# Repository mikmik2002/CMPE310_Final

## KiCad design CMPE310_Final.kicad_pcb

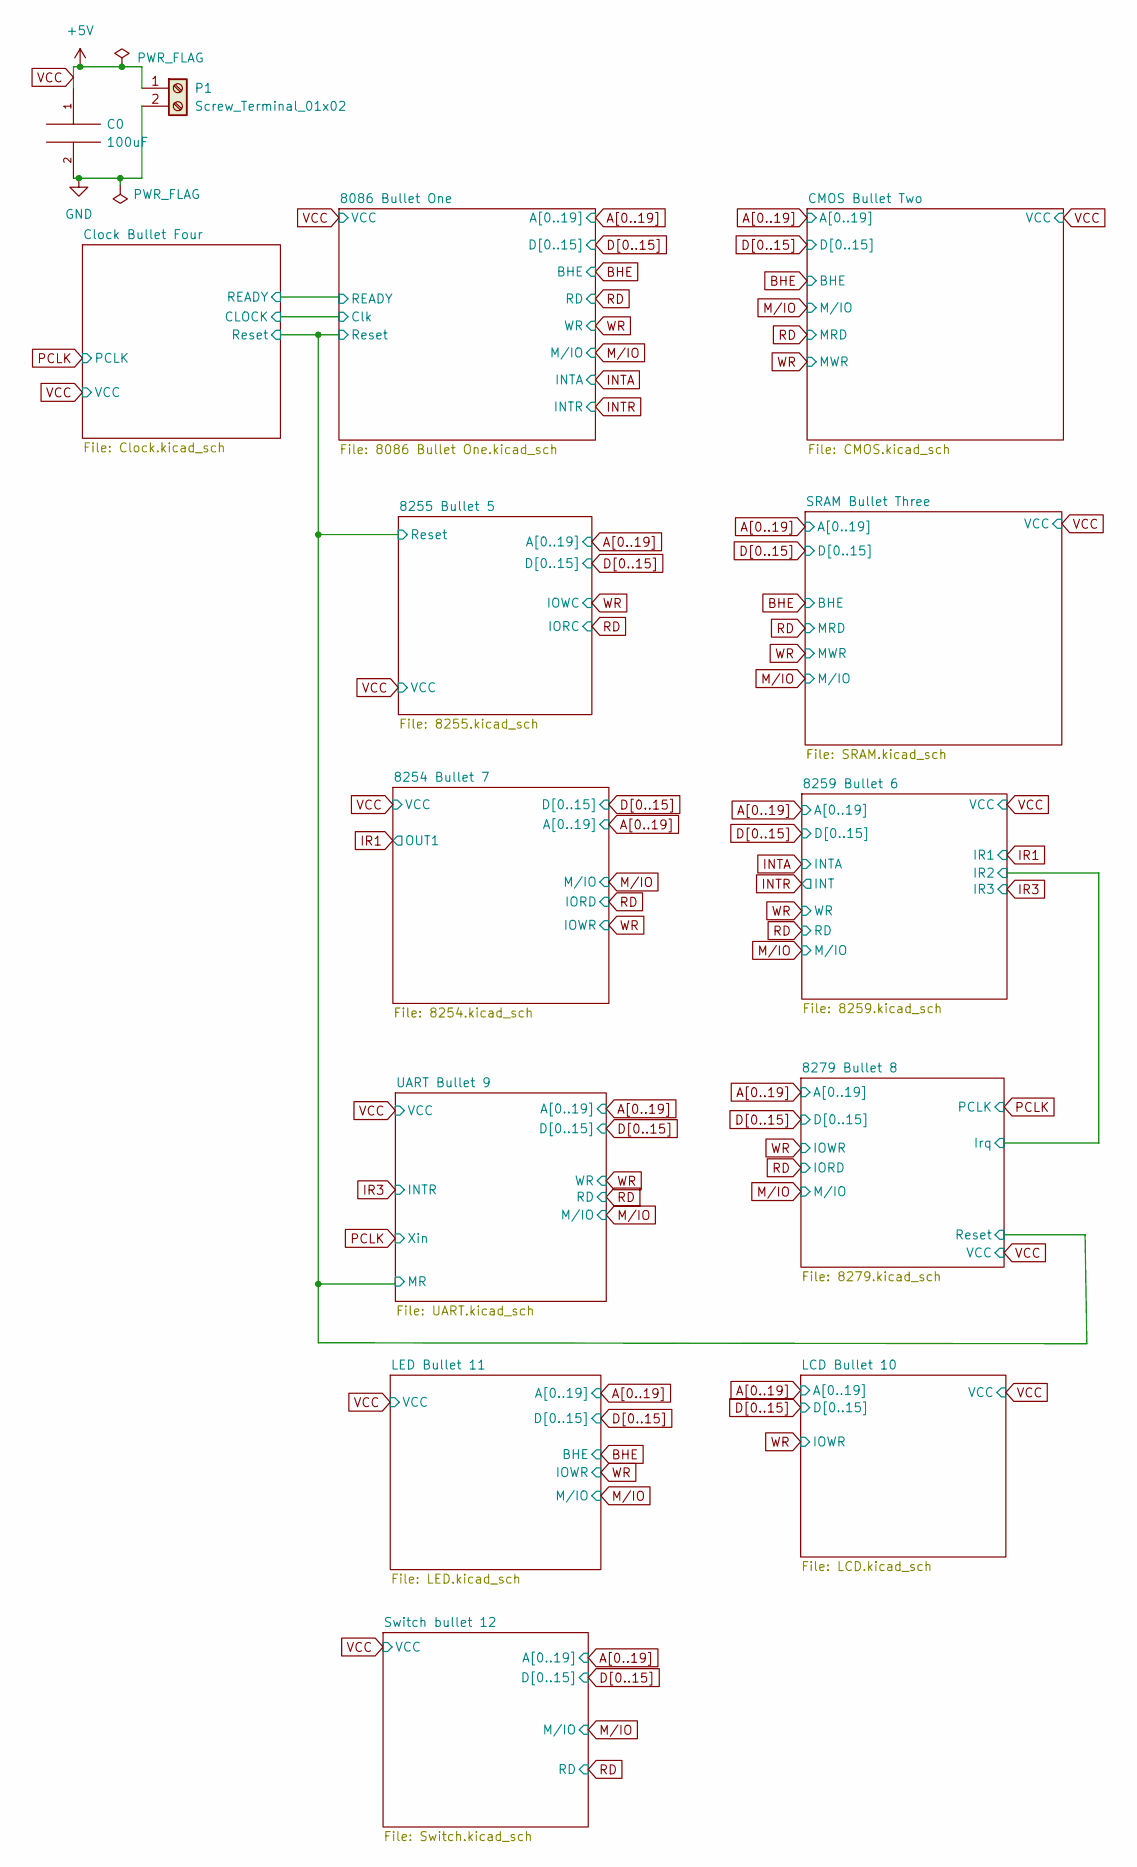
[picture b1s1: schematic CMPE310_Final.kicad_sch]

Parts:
C0: 100uF; CP_Axial_L10.0mm_D4.5mm_P15.00mm_Horizontal
P1: Screw_Terminal_01x02; TerminalBlock_Altech_AK300-2_P5.00mm

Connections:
GND: C0.2, P1.2; also elsewhere on the board
VCC: C0.1, P1.1; also elsewhere on the board

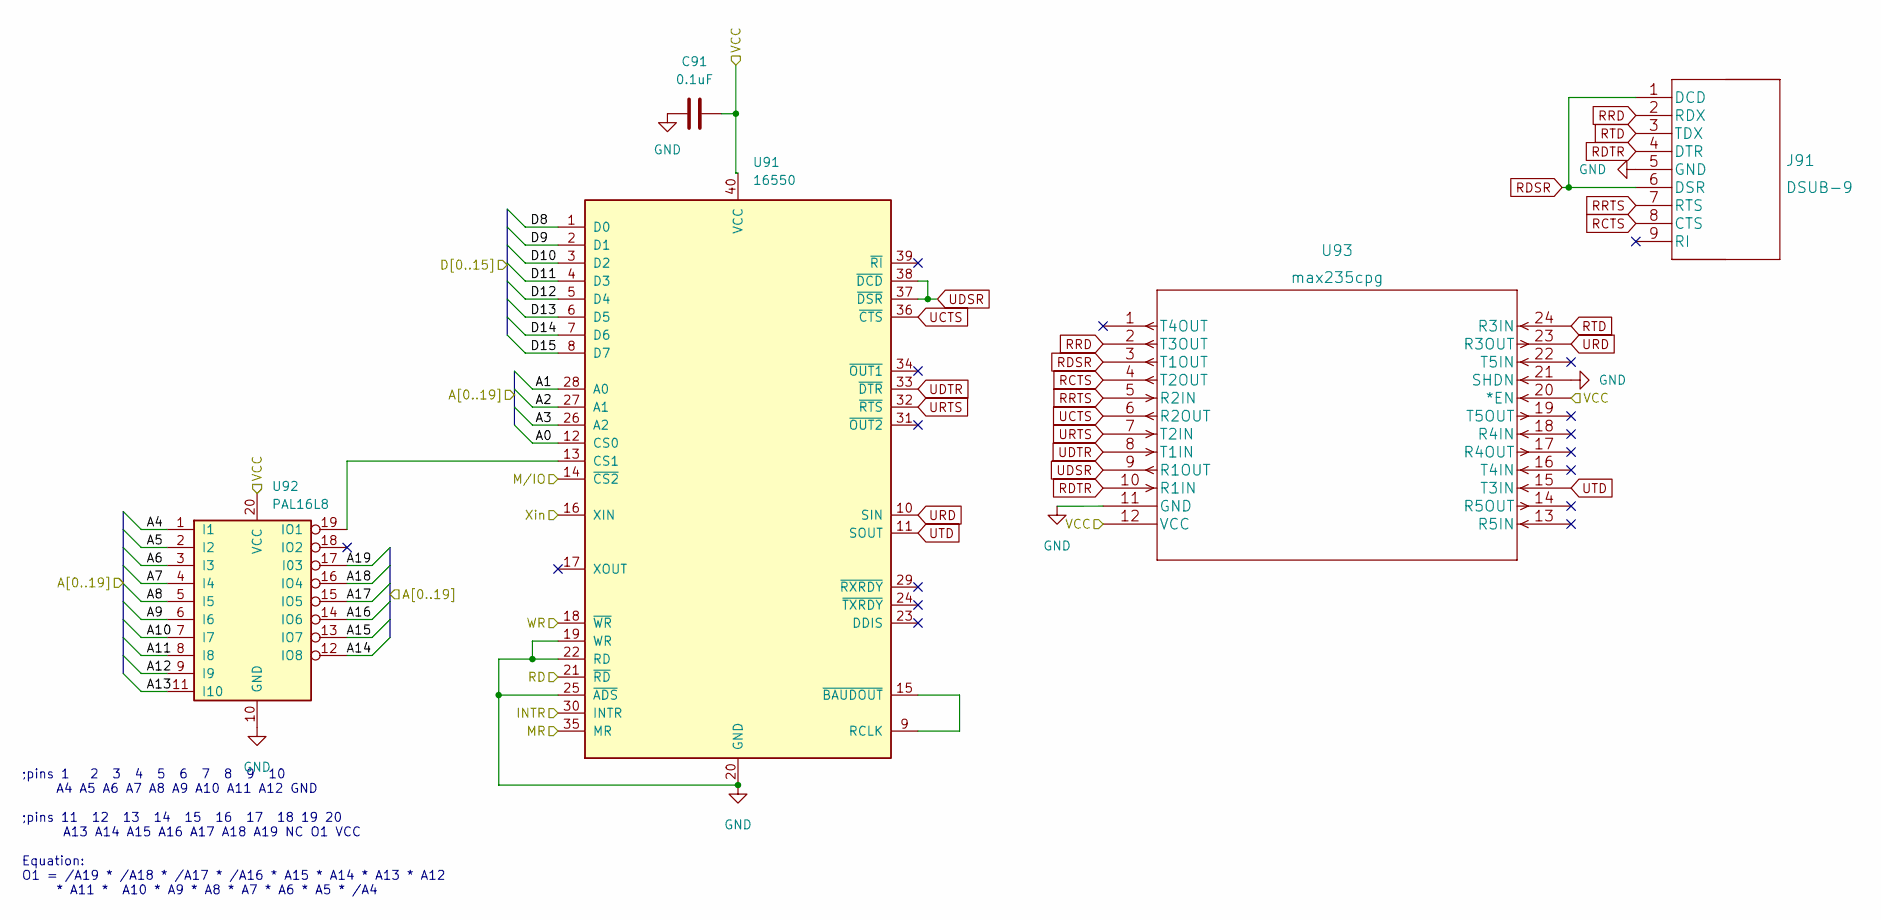
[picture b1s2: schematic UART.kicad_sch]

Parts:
C91: 0.1uF; C_Axial_L3.8mm_D2.6mm_P7.50mm_Horizontal
J91: DSUB-9
U91: 16550; DIP-40_W15.24mm
U92: PAL16L8; DIP-20_W7.62mm
U93: max235cpg

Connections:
/8086 Bullet One/Reset: U91.35 (MR); also elsewhere on the board
A0: U91.12 (CS0); also elsewhere on the board
A1: U91.28 (A0); also elsewhere on the board
A2: U91.27 (A1); also elsewhere on the board
A3: U91.26 (A2); also elsewhere on the board
A4: U92.1 (I1); also elsewhere on the board
A5: U92.2 (I2); also elsewhere on the board
A6: U92.3 (I3); also elsewhere on the board
A7: U92.4 (I4); also elsewhere on the board
A8: U92.5 (I5); also elsewhere on the board
A9: U92.6 (I6); also elsewhere on the board
A10: U92.7 (I7); also elsewhere on the board
A11: U92.8 (I8); also elsewhere on the board
A12: U92.9 (I9); also elsewhere on the board
A13: U92.11 (I10); also elsewhere on the board
A14: U92.12 (IO8); also elsewhere on the board
A15: U92.13 (IO7); also elsewhere on the board
A16: U92.14 (IO6); also elsewhere on the board
A17: U92.15 (IO5); also elsewhere on the board
A18: U92.16 (IO4); also elsewhere on the board
A19: U92.17 (I03); also elsewhere on the board
D8: U91.1 (D0); also elsewhere on the board
D9: U91.2 (D1); also elsewhere on the board
D10: U91.3 (D2); also elsewhere on the board
D11: U91.4 (D3); also elsewhere on the board
D12: U91.5 (D4); also elsewhere on the board
D13: U91.6 (D5); also elsewhere on the board
D14: U91.7 (D6); also elsewhere on the board
D15: U91.8 (D7); also elsewhere on the board
GND: C91.1, J91.5 (GND), U91.19 (WR), U91.20 (GND), U91.22 (RD), U91.25 (~ADS), U92.10 (GND), U93.11 (GND), U93.21 (SHDN); also elsewhere on the board
IR3: U91.30 (INTR); also elsewhere on the board
M/IO: U91.14 (~CS2); also elsewhere on the board
unnamed: U91.13 (CS1), U92.19 (IO1)
unnamed: U91.9 (RCLK), U91.15 (~BAUDOUT)
PCLK: U91.16 (XIN); also elsewhere on the board
RCTS: J91.8 (CTS), U93.4 (T2OUT)
RD: U91.21 (~RD); also elsewhere on the board
RDSR: J91.1 (DCD), J91.6 (DSR), U93.3 (T1OUT)
RDTR: J91.4 (DTR), U93.10 (R1IN)
RRD: J91.2 (RDX), U93.2 (T3OUT)
RRTS: J91.7 (RTS), U93.5 (R2IN)
RTD: J91.3 (TDX), U93.24 (R3IN)
UCTS: U91.36 (~CTS), U93.6 (R2OUT)
UDSR: U91.37 (~DSR), U91.38 (~DCD), U93.9 (R1OUT)
UDTR: U91.33 (~DTR), U93.8 (T1IN)
URD: U91.10 (SIN), U93.23 (R3OUT)
URTS: U91.32 (~RTS), U93.7 (T2IN)
UTD: U91.11 (SOUT), U93.15 (T3IN)
VCC: C91.2, U91.40 (VCC), U92.20 (VCC), U93.12 (VCC), U93.20 (*EN); also elsewhere on the board
WR: U91.18 (~WR); also elsewhere on the board

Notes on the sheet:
;pins 1 2 3 4 5 6 7 8 9 10 A4 A5 A6 A7 A8 A9 A10 A11 A12 GND ;pins 11 12 13 14 15 16 17 18 19 20 A13 A14 A15 A16 A17 A18 A19 NC O1 VCC Equation: O1 = /A19 * /A18 * /A17 * /A16 * A15 * A14 * A13 * A12 * A11 * A10 * A9 * A8 * A7 * A6 * A5 * /A4

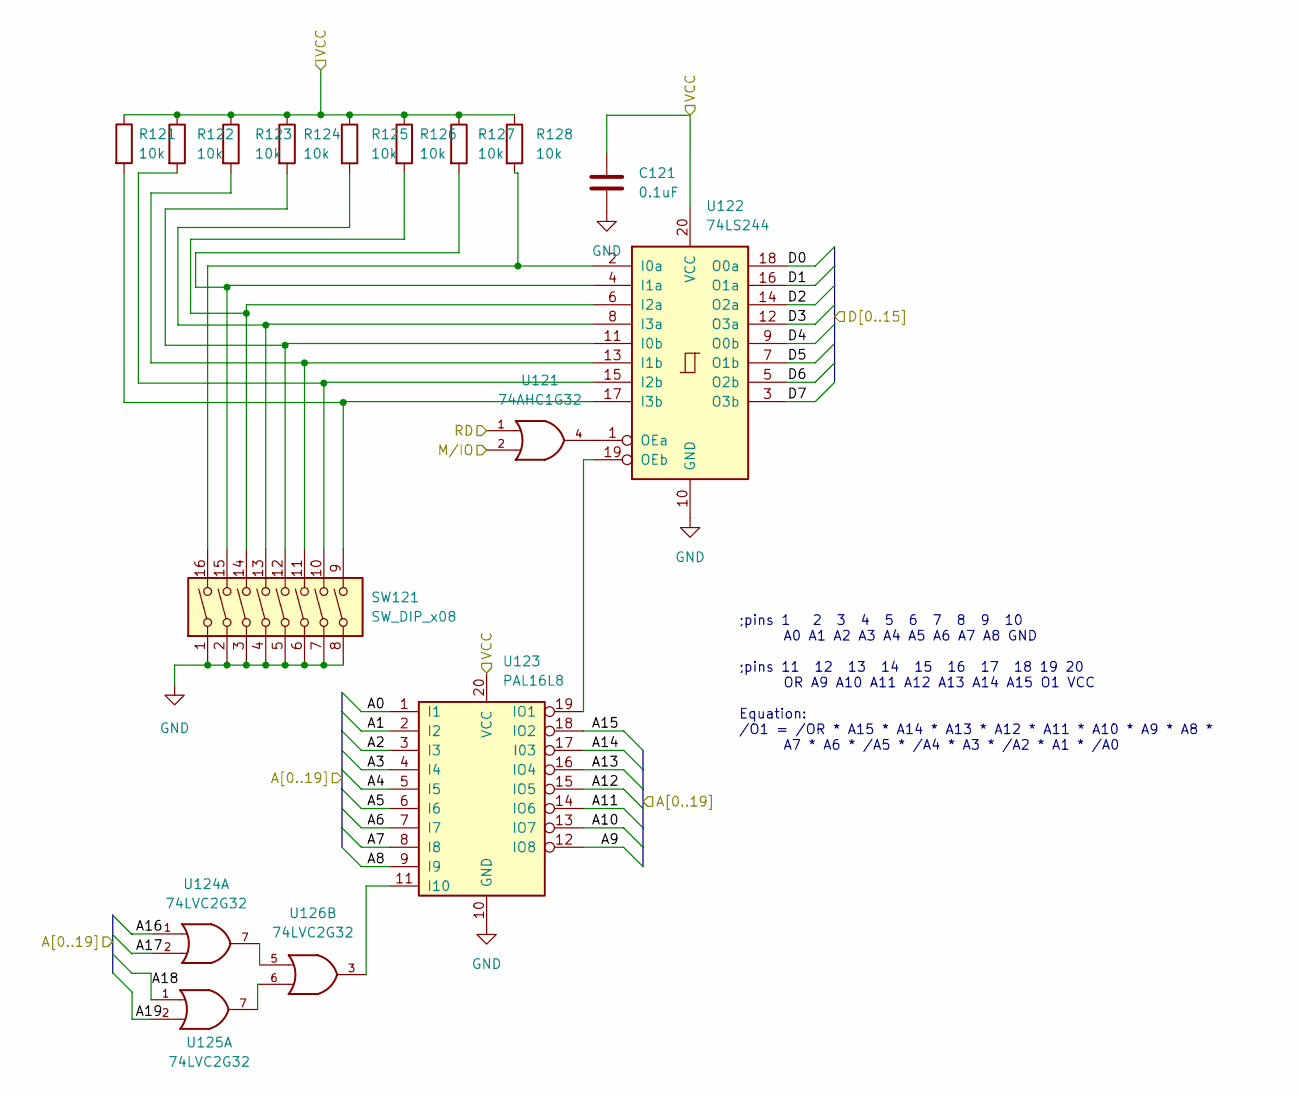
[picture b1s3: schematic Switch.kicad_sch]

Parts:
C121: 0.1uF; C_Axial_L3.8mm_D2.6mm_P7.50mm_Horizontal
R121, R122, R123, R124, R125, R126, R127, R128: 10k; R_Axial_DIN0204_L3.6mm_D1.6mm_P1.90mm_Vertical
SW121: SW_DIP_x08; SW_DIP_SPSTx08_Slide_6.7x21.88mm_W7.62mm_P2.54mm_LowProfile
U121: 74AHC1G32; SOT-23-5
U122: 74LS244; DIP-20_W7.62mm
U123: PAL16L8; DIP-20_W7.62mm
U124, U125, U126: 74LVC2G32

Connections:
A0: U123.1 (I1); also elsewhere on the board
A1: U123.2 (I2); also elsewhere on the board
A2: U123.3 (I3); also elsewhere on the board
A3: U123.4 (I4); also elsewhere on the board
A4: U123.5 (I5); also elsewhere on the board
A5: U123.6 (I6); also elsewhere on the board
A6: U123.7 (I7); also elsewhere on the board
A7: U123.8 (I8); also elsewhere on the board
A8: U123.9 (I9); also elsewhere on the board
A9: U123.12 (IO8); also elsewhere on the board
A10: U123.13 (IO7); also elsewhere on the board
A11: U123.14 (IO6); also elsewhere on the board
A12: U123.15 (IO5); also elsewhere on the board
A13: U123.16 (IO4); also elsewhere on the board
A14: U123.17 (I03); also elsewhere on the board
A15: U123.18 (IO2); also elsewhere on the board
A16: U124.1; also elsewhere on the board
A17: U124.2; also elsewhere on the board
A18: U125.1; also elsewhere on the board
A19: U125.2; also elsewhere on the board
D0: U122.18 (O0a); also elsewhere on the board
D1: U122.16 (O1a); also elsewhere on the board
D2: U122.14 (O2a); also elsewhere on the board
D3: U122.12 (O3a); also elsewhere on the board
D4: U122.9 (O0b); also elsewhere on the board
D5: U122.7 (O1b); also elsewhere on the board
D6: U122.5 (O2b); also elsewhere on the board
D7: U122.3 (O3b); also elsewhere on the board
GND: C121.2, SW121.1, SW121.2, SW121.3, SW121.4, SW121.5, SW121.6, SW121.7, SW121.8, U121.3 (GND), U122.10 (GND), U123.10 (GND), U124.4 (GND), U125.4 (GND), U126.4 (GND); also elsewhere on the board
M/IO: U121.2; also elsewhere on the board
unnamed: R121.2, SW121.9, U122.17 (I3b)
unnamed: R122.2, SW121.10, U122.15 (I2b)
unnamed: R123.2, SW121.11, U122.13 (I1b)
unnamed: R124.2, SW121.12, U122.11 (I0b)
unnamed: R125.2, SW121.13, U122.8 (I3a)
unnamed: R126.2, SW121.14, U122.6 (I2a)
unnamed: R127.2, SW121.15, U122.4 (I1a)
unnamed: R128.2, SW121.16, U122.2 (I0a)
unnamed: U121.4, U122.1 (OEa)
unnamed: U122.19 (OEb), U123.19 (IO1)
unnamed: U123.11 (I10), U126.3
unnamed: U124.7, U126.5
unnamed: U125.7, U126.6
RD: U121.1; also elsewhere on the board
VCC: C121.1, R121.1, R122.1, R123.1, R124.1, R125.1, R126.1, R127.1, R128.1, U121.5 (VCC), U122.20 (VCC), U123.20 (VCC), U124.8 (VCC), U125.8 (VCC), U126.8 (VCC); also elsewhere on the board

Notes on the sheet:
;pins 1 2 3 4 5 6 7 8 9 10 A0 A1 A2 A3 A4 A5 A6 A7 A8 GND ;pins 11 12 13 14 15 16 17 18 19 20 OR A9 A10 A11 A12 A13 A14 A15 O1 VCC Equation: /O1 = /OR * A15 * A14 * A13 * A12 * A11 * A10 * A9 * A8 * A7 * A6 * /A5 * /A4 * A3 * /A2 * A1 * /A0

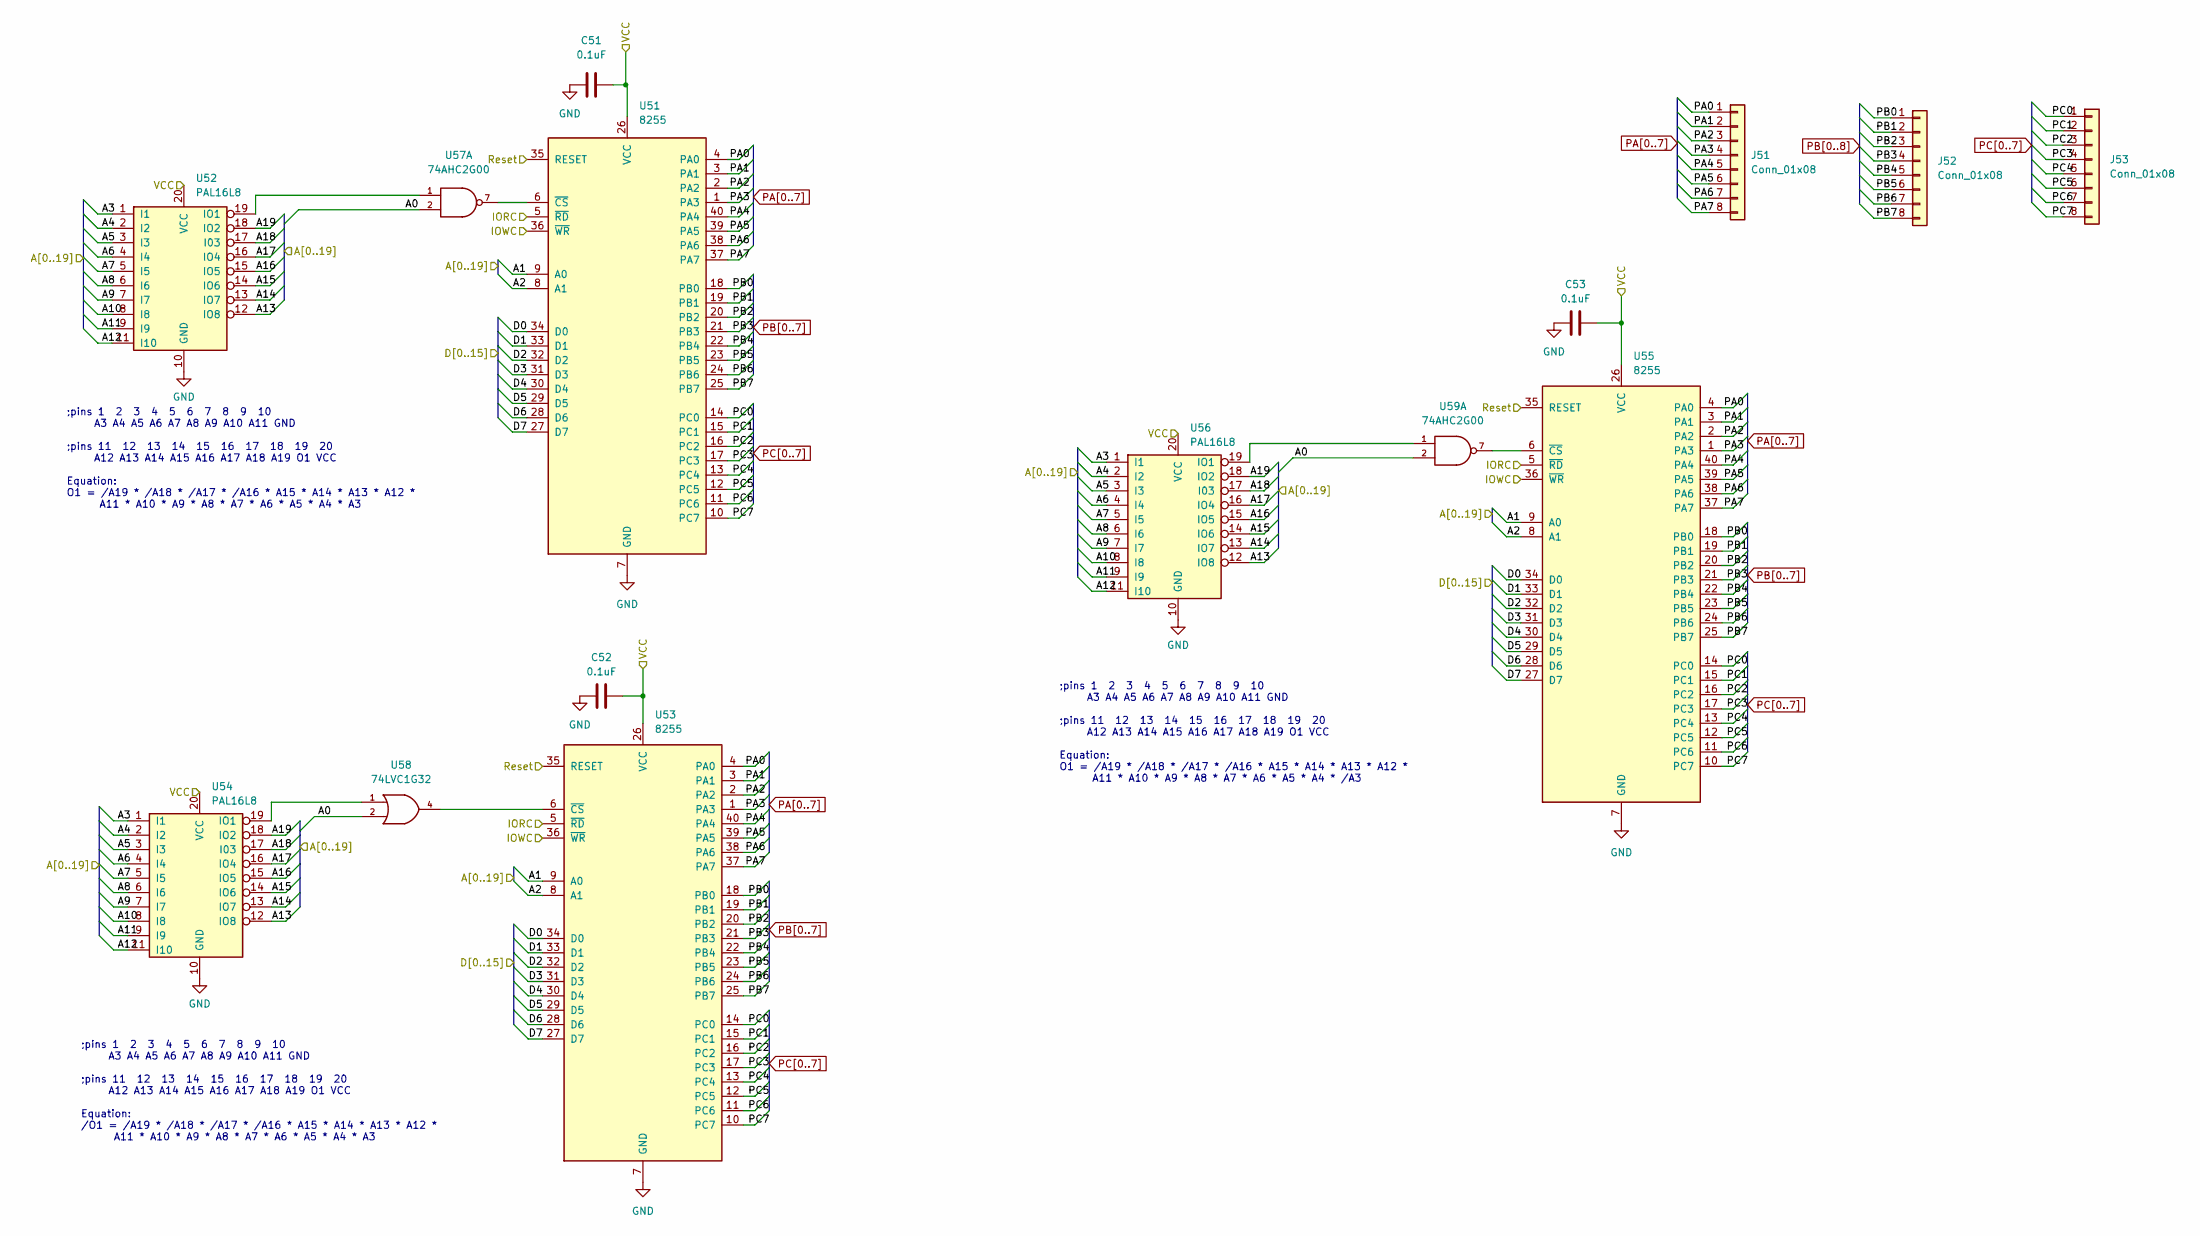
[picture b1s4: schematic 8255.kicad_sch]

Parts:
C51, C52, C53: 0.1uF; C_Axial_L3.8mm_D2.6mm_P7.50mm_Horizontal
J51, J52, J53: Conn_01x08; PinHeader_1x08_P1.00mm_Vertical
U51, U53, U55: 8255; DIP-40_W15.24mm
U52, U54, U56: PAL16L8; DIP-20_W7.62mm
U57, U59: 74AHC2G00
U58: 74LVC1G32

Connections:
/8086 Bullet One/Reset: U51.35 (RESET), U53.35 (RESET), U55.35 (RESET); also elsewhere on the board
A0: U57.2, U58.2, U59.2; also elsewhere on the board
A1: U51.9 (A0), U53.9 (A0), U55.9 (A0); also elsewhere on the board
A2: U51.8 (A1), U53.8 (A1), U55.8 (A1); also elsewhere on the board
A3: U52.1 (I1), U54.1 (I1), U56.1 (I1); also elsewhere on the board
A4: U52.2 (I2), U54.2 (I2), U56.2 (I2); also elsewhere on the board
A5: U52.3 (I3), U54.3 (I3), U56.3 (I3); also elsewhere on the board
A6: U52.4 (I4), U54.4 (I4), U56.4 (I4); also elsewhere on the board
A7: U52.5 (I5), U54.5 (I5), U56.5 (I5); also elsewhere on the board
A8: U52.6 (I6), U54.6 (I6), U56.6 (I6); also elsewhere on the board
A9: U52.7 (I7), U54.7 (I7), U56.7 (I7); also elsewhere on the board
A10: U52.8 (I8), U54.8 (I8), U56.8 (I8); also elsewhere on the board
A11: U52.9 (I9), U54.9 (I9), U56.9 (I9); also elsewhere on the board
A12: U52.11 (I10), U54.11 (I10), U56.11 (I10); also elsewhere on the board
A13: U52.12 (IO8), U54.12 (IO8), U56.12 (IO8); also elsewhere on the board
A14: U52.13 (IO7), U54.13 (IO7), U56.13 (IO7); also elsewhere on the board
A15: U52.14 (IO6), U54.14 (IO6), U56.14 (IO6); also elsewhere on the board
A16: U52.15 (IO5), U54.15 (IO5), U56.15 (IO5); also elsewhere on the board
A17: U52.16 (IO4), U54.16 (IO4), U56.16 (IO4); also elsewhere on the board
A18: U52.17 (I03), U54.17 (I03), U56.17 (I03); also elsewhere on the board
A19: U52.18 (IO2), U54.18 (IO2), U56.18 (IO2); also elsewhere on the board
D0: U51.34 (D0), U53.34 (D0), U55.34 (D0); also elsewhere on the board
D1: U51.33 (D1), U53.33 (D1), U55.33 (D1); also elsewhere on the board
D2: U51.32 (D2), U53.32 (D2), U55.32 (D2); also elsewhere on the board
D3: U51.31 (D3), U53.31 (D3), U55.31 (D3); also elsewhere on the board
D4: U51.30 (D4), U53.30 (D4), U55.30 (D4); also elsewhere on the board
D5: U51.29 (D5), U53.29 (D5), U55.29 (D5); also elsewhere on the board
D6: U51.28 (D6), U53.28 (D6), U55.28 (D6); also elsewhere on the board
D7: U51.27 (D7), U53.27 (D7), U55.27 (D7); also elsewhere on the board
GND: C51.1, C52.1, C53.1, U51.7 (GND), U52.10 (GND), U53.7 (GND), U54.10 (GND), U55.7 (GND), U56.10 (GND), U57.4 (GND), U58.3 (GND), U59.4 (GND); also elsewhere on the board
unnamed: U51.6 (~CS), U57.7
unnamed: U52.19 (IO1), U57.1
unnamed: U53.6 (~CS), U58.4
unnamed: U54.19 (IO1), U58.1
unnamed: U55.6 (~CS), U59.7
unnamed: U56.19 (IO1), U59.1
PA0: J51.1, U51.4 (PA0), U53.4 (PA0), U55.4 (PA0)
PA1: J51.2, U51.3 (PA1), U53.3 (PA1), U55.3 (PA1)
PA2: J51.3, U51.2 (PA2), U53.2 (PA2), U55.2 (PA2)
PA3: J51.4, U51.1 (PA3), U53.1 (PA3), U55.1 (PA3)
PA4: J51.5, U51.40 (PA4), U53.40 (PA4), U55.40 (PA4)
PA5: J51.6, U51.39 (PA5), U53.39 (PA5), U55.39 (PA5)
PA6: J51.7, U51.38 (PA6), U53.38 (PA6), U55.38 (PA6)
PA7: J51.8, U51.37 (PA7), U53.37 (PA7), U55.37 (PA7)
PB0: J52.1, U51.18 (PB0), U53.18 (PB0), U55.18 (PB0)
PB1: J52.2, U51.19 (PB1), U53.19 (PB1), U55.19 (PB1)
PB2: J52.3, U51.20 (PB2), U53.20 (PB2), U55.20 (PB2)
PB3: J52.4, U51.21 (PB3), U53.21 (PB3), U55.21 (PB3)
PB4: J52.5, U51.22 (PB4), U53.22 (PB4), U55.22 (PB4)
PB5: J52.6, U51.23 (PB5), U53.23 (PB5), U55.23 (PB5)
PB6: J52.7, U51.24 (PB6), U53.24 (PB6), U55.24 (PB6)
PB7: J52.8, U51.25 (PB7), U53.25 (PB7), U55.25 (PB7)
PC0: J53.1, U51.14 (PC0), U53.14 (PC0), U55.14 (PC0)
PC1: J53.2, U51.15 (PC1), U53.15 (PC1), U55.15 (PC1)
PC2: J53.3, U51.16 (PC2), U53.16 (PC2), U55.16 (PC2)
PC3: J53.4, U51.17 (PC3), U53.17 (PC3), U55.17 (PC3)
PC4: J53.5, U51.13 (PC4), U53.13 (PC4), U55.13 (PC4)
PC5: J53.6, U51.12 (PC5), U53.12 (PC5), U55.12 (PC5)
PC6: J53.7, U51.11 (PC6), U53.11 (PC6), U55.11 (PC6)
PC7: J53.8, U51.10 (PC7), U53.10 (PC7), U55.10 (PC7)
RD: U51.5 (~RD), U53.5 (~RD), U55.5 (~RD); also elsewhere on the board
VCC: C51.2, C52.2, C53.2, U51.26 (VCC), U52.20 (VCC), U53.26 (VCC), U54.20 (VCC), U55.26 (VCC), U56.20 (VCC), U57.8 (VCC), U59.8 (VCC); also elsewhere on the board
WR: U51.36 (~WR), U53.36 (~WR), U55.36 (~WR); also elsewhere on the board

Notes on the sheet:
;pins 1 2 3 4 5 6 7 8 9 10 A3 A4 A5 A6 A7 A8 A9 A10 A11 GND ;pins 11 12 13 14 15 16 17 18 19 20 A12 A13 A14 A15 A16 A17 A18 A19 O1 VCC Equation: O1 = /A19 * /A18 * /A17 * /A16 * A15 * A14 * A13 * A12 * A11 * A10 * A9 * A8 * A7 * A6 * A5 * A4 * A3
;pins 1 2 3 4 5 6 7 8 9 10 A3 A4 A5 A6 A7 A8 A9 A10 A11 GND ;pins 11 12 13 14 15 16 17 18 19 20 A12 A13 A14 A15 A16 A17 A18 A19 O1 VCC Equation: /O1 = /A19 * /A18 * /A17 * /A16 * A15 * A14 * A13 * A12 * A11 * A10 * A9 * A8 * A7 * A6 * A5 * A4 * A3
;pins 1 2 3 4 5 6 7 8 9 10 A3 A4 A5 A6 A7 A8 A9 A10 A11 GND ;pins 11 12 13 14 15 16 17 18 19 20 A12 A13 A14 A15 A16 A17 A18 A19 O1 VCC Equation: O1 = /A19 * /A18 * /A17 * /A16 * A15 * A14 * A13 * A12 * A11 * A10 * A9 * A8 * A7 * A6 * A5 * A4 * /A3

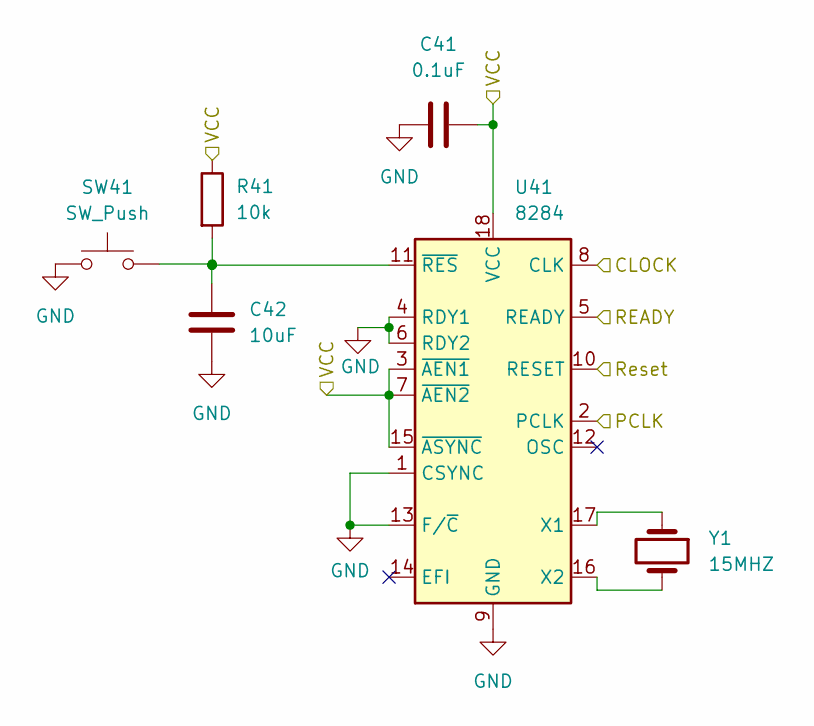
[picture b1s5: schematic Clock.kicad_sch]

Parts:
C41: 0.1uF; C_Axial_L3.8mm_D2.6mm_P7.50mm_Horizontal
C42: 10uF; C_Axial_L3.8mm_D2.6mm_P7.50mm_Horizontal
R41: 10k; R_Axial_DIN0204_L3.6mm_D1.6mm_P1.90mm_Vertical
SW41: SW_Push; SW_Tactile_Straight_KSA0Axx1LFTR
U41: 8284; DIP-18_W7.62mm
Y1: 15MHZ; Crystal_AT310_D3.0mm_L10.0mm_Vertical

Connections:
/8086 Bullet One/Clk: U41.8 (CLK); also elsewhere on the board
/8086 Bullet One/READY: U41.5 (READY); also elsewhere on the board
/8086 Bullet One/Reset: U41.10 (RESET); also elsewhere on the board
GND: C41.1, C42.2, SW41.1, U41.1 (CSYNC), U41.4 (RDY1), U41.6 (RDY2), U41.9 (GND), U41.13 (F/~C); also elsewhere on the board
unnamed: C42.1, R41.2, SW41.2, U41.11 (~RES)
unnamed: U41.16 (X2), Y1.2
unnamed: U41.17 (X1), Y1.1
PCLK: U41.2 (PCLK); also elsewhere on the board
VCC: C41.2, R41.1, U41.3 (~AEN1), U41.7 (~AEN2), U41.15 (~ASYNC), U41.18 (VCC); also elsewhere on the board

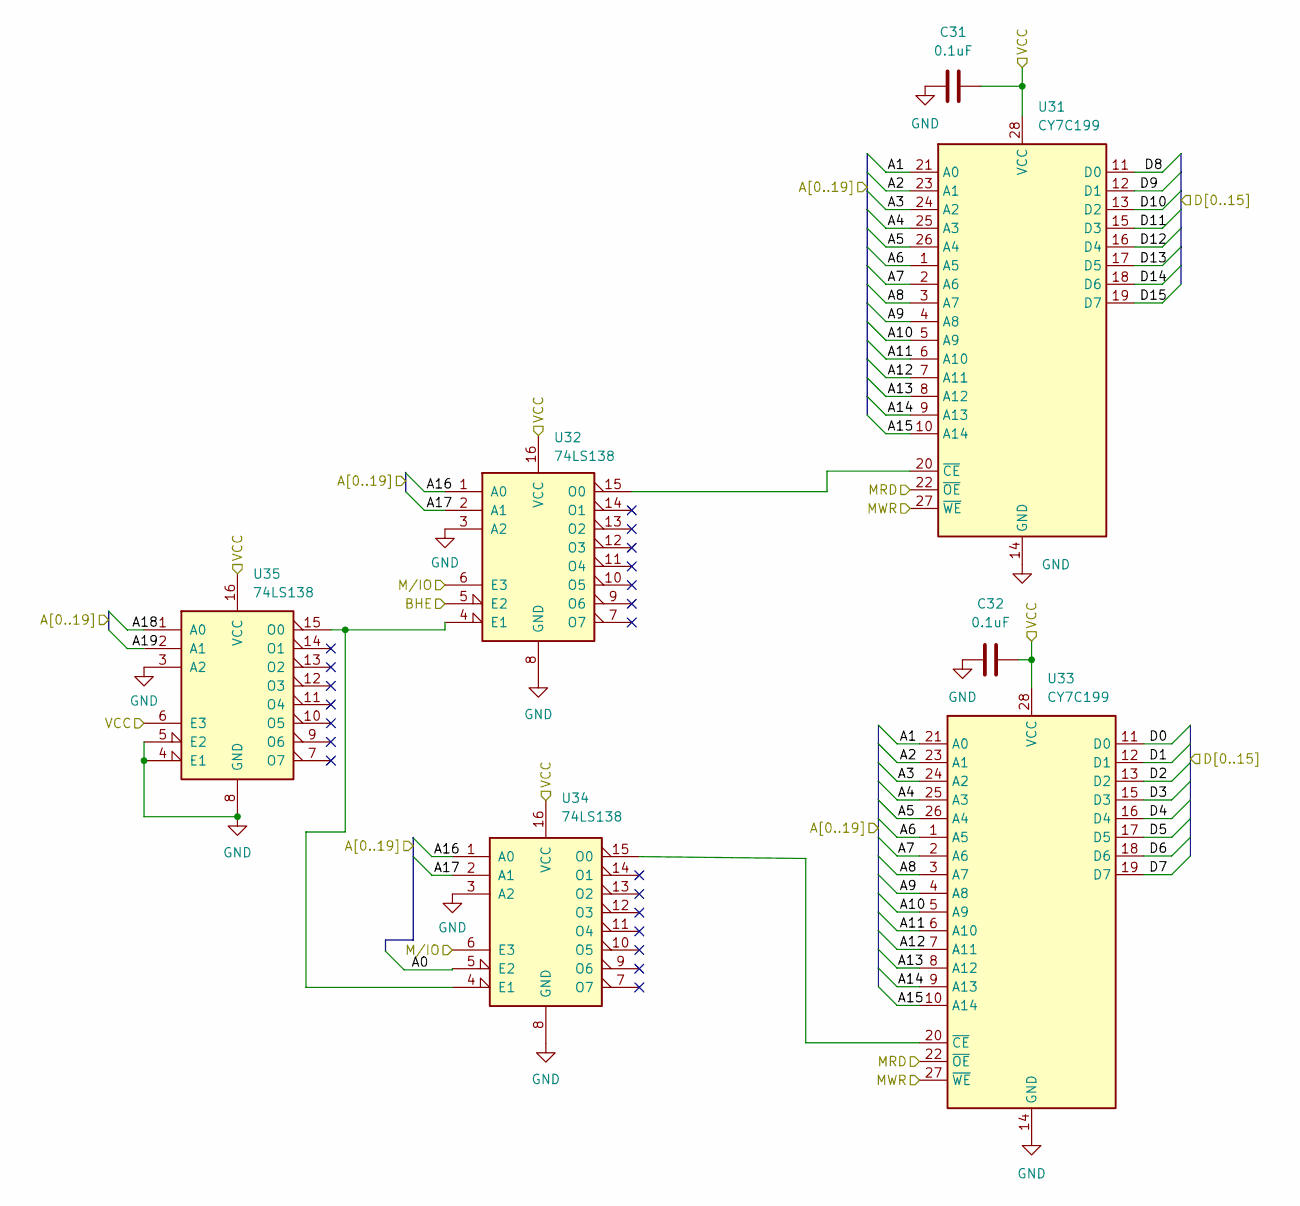
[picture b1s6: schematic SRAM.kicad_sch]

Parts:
C31, C32: 0.1uF; C_Axial_L3.8mm_D2.6mm_P7.50mm_Horizontal
U31, U33: CY7C199; DIP-28_W7.62mm
U32, U34, U35: 74LS138; DIP-16_W7.62mm

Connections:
A0: U34.5 (E2); also elsewhere on the board
A1: U31.21 (A0), U33.21 (A0); also elsewhere on the board
A2: U31.23 (A1), U33.23 (A1); also elsewhere on the board
A3: U31.24 (A2), U33.24 (A2); also elsewhere on the board
A4: U31.25 (A3), U33.25 (A3); also elsewhere on the board
A5: U31.26 (A4), U33.26 (A4); also elsewhere on the board
A6: U31.1 (A5), U33.1 (A5); also elsewhere on the board
A7: U31.2 (A6), U33.2 (A6); also elsewhere on the board
A8: U31.3 (A7), U33.3 (A7); also elsewhere on the board
A9: U31.4 (A8), U33.4 (A8); also elsewhere on the board
A10: U31.5 (A9), U33.5 (A9); also elsewhere on the board
A11: U31.6 (A10), U33.6 (A10); also elsewhere on the board
A12: U31.7 (A11), U33.7 (A11); also elsewhere on the board
A13: U31.8 (A12), U33.8 (A12); also elsewhere on the board
A14: U31.9 (A13), U33.9 (A13); also elsewhere on the board
A15: U31.10 (A14), U33.10 (A14); also elsewhere on the board
A16: U32.1 (A0), U34.1 (A0); also elsewhere on the board
A17: U32.2 (A1), U34.2 (A1); also elsewhere on the board
A18: U35.1 (A0); also elsewhere on the board
A19: U35.2 (A1); also elsewhere on the board
BHE: U32.5 (E2); also elsewhere on the board
D0: U33.11 (D0); also elsewhere on the board
D1: U33.12 (D1); also elsewhere on the board
D2: U33.13 (D2); also elsewhere on the board
D3: U33.15 (D3); also elsewhere on the board
D4: U33.16 (D4); also elsewhere on the board
D5: U33.17 (D5); also elsewhere on the board
D6: U33.18 (D6); also elsewhere on the board
D7: U33.19 (D7); also elsewhere on the board
D8: U31.11 (D0); also elsewhere on the board
D9: U31.12 (D1); also elsewhere on the board
D10: U31.13 (D2); also elsewhere on the board
D11: U31.15 (D3); also elsewhere on the board
D12: U31.16 (D4); also elsewhere on the board
D13: U31.17 (D5); also elsewhere on the board
D14: U31.18 (D6); also elsewhere on the board
D15: U31.19 (D7); also elsewhere on the board
GND: C31.1, C32.1, U31.14 (GND), U32.3 (A2), U32.8 (GND), U33.14 (GND), U34.3 (A2), U34.8 (GND), U35.3 (A2), U35.4 (E1), U35.5 (E2), U35.8 (GND); also elsewhere on the board
M/IO: U32.6 (E3), U34.6 (E3); also elsewhere on the board
unnamed: U31.20 (~CE), U32.15 (O0)
unnamed: U32.4 (E1), U34.4 (E1), U35.15 (O0)
unnamed: U33.20 (~CE), U34.15 (O0)
RD: U31.22 (~OE), U33.22 (~OE); also elsewhere on the board
VCC: C31.2, C32.2, U31.28 (VCC), U32.16 (VCC), U33.28 (VCC), U34.16 (VCC), U35.6 (E3), U35.16 (VCC); also elsewhere on the board
WR: U31.27 (~WE), U33.27 (~WE); also elsewhere on the board

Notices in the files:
parts and their libraries:
Copyright 2016 Accelerated Designs. All rights reserved.
